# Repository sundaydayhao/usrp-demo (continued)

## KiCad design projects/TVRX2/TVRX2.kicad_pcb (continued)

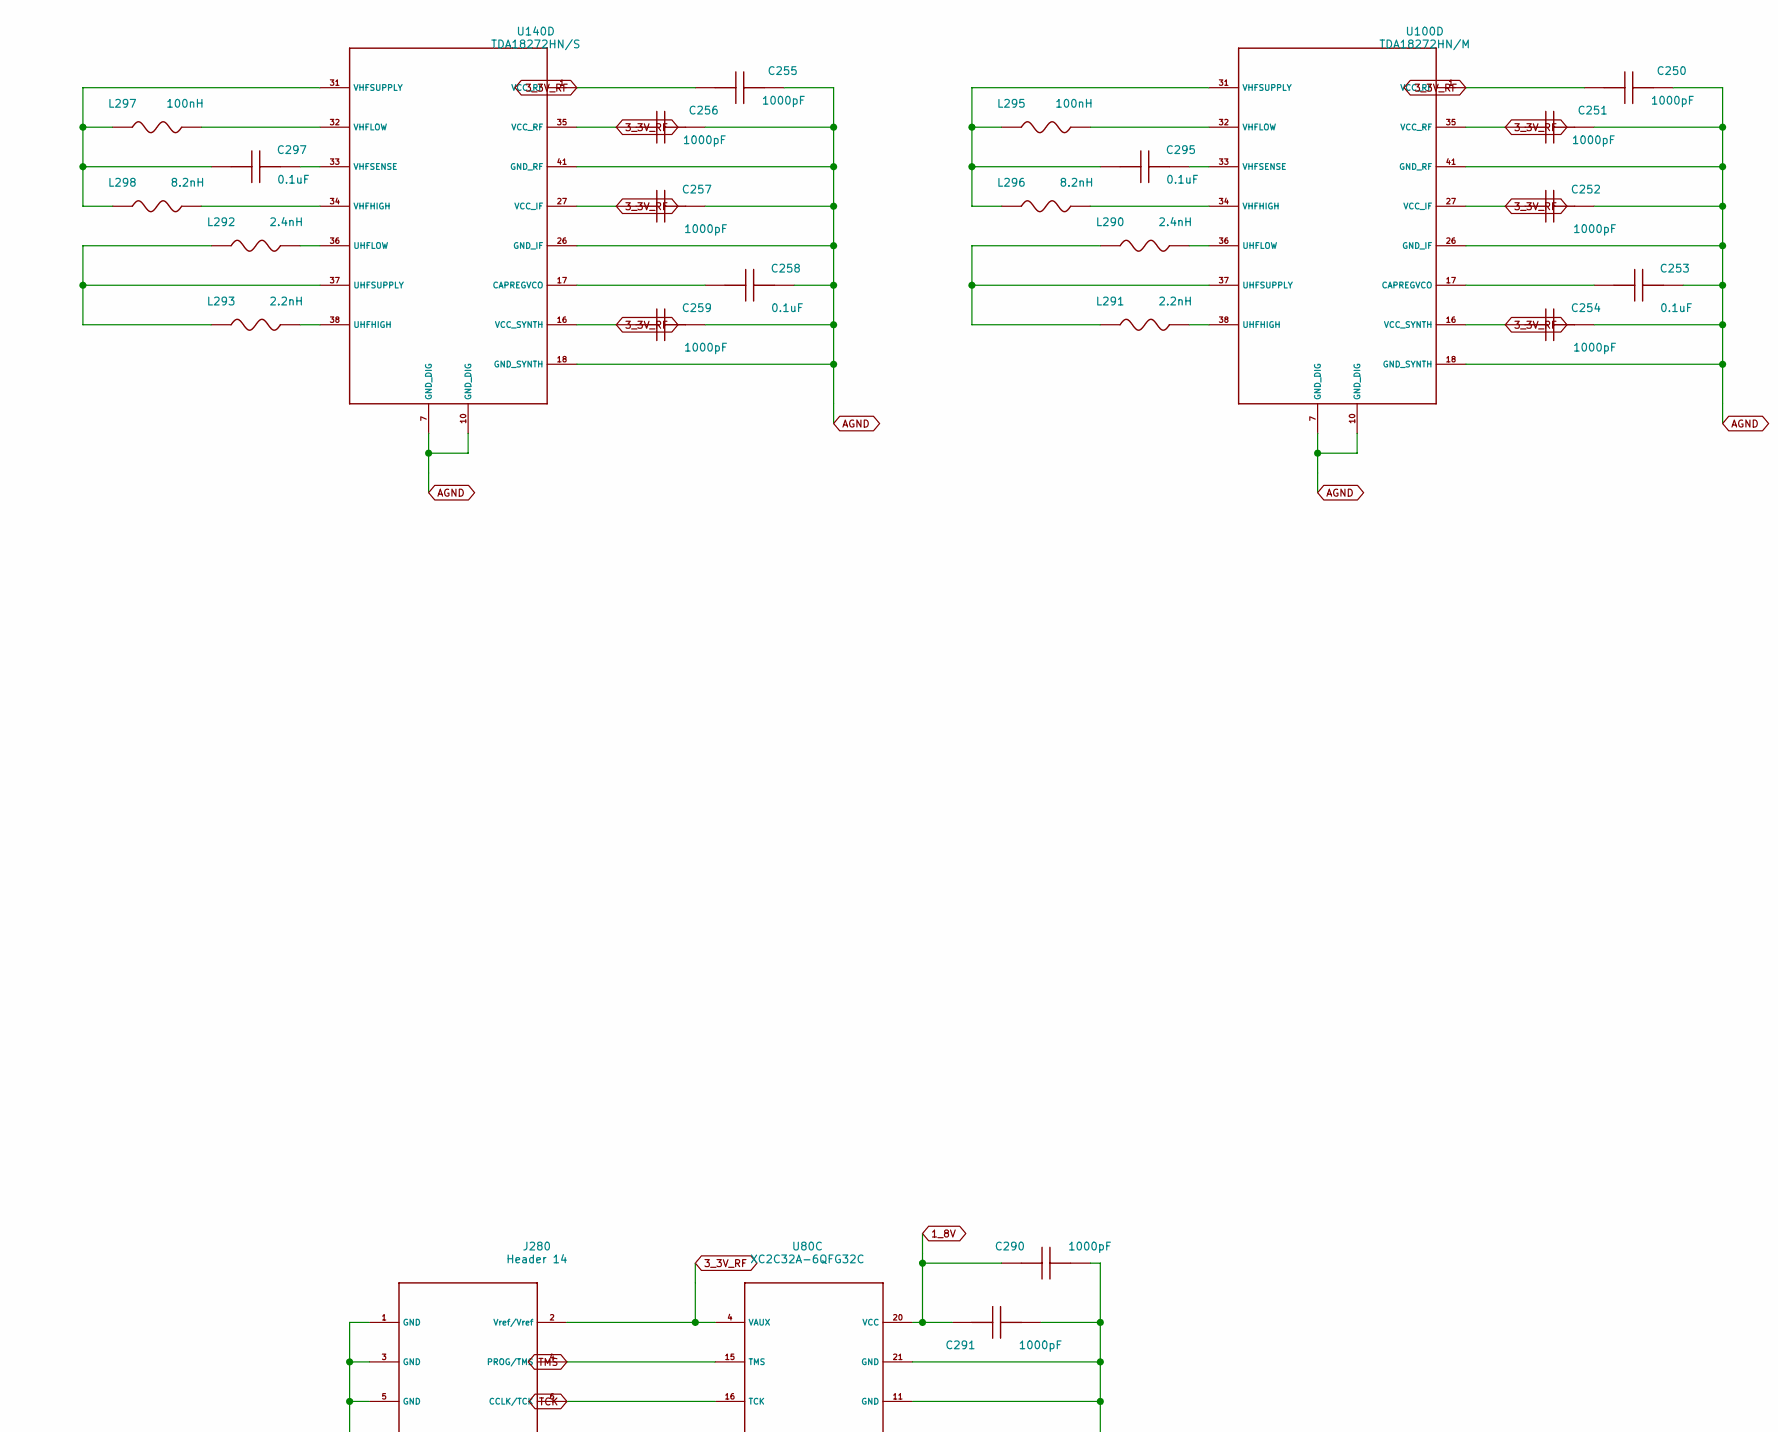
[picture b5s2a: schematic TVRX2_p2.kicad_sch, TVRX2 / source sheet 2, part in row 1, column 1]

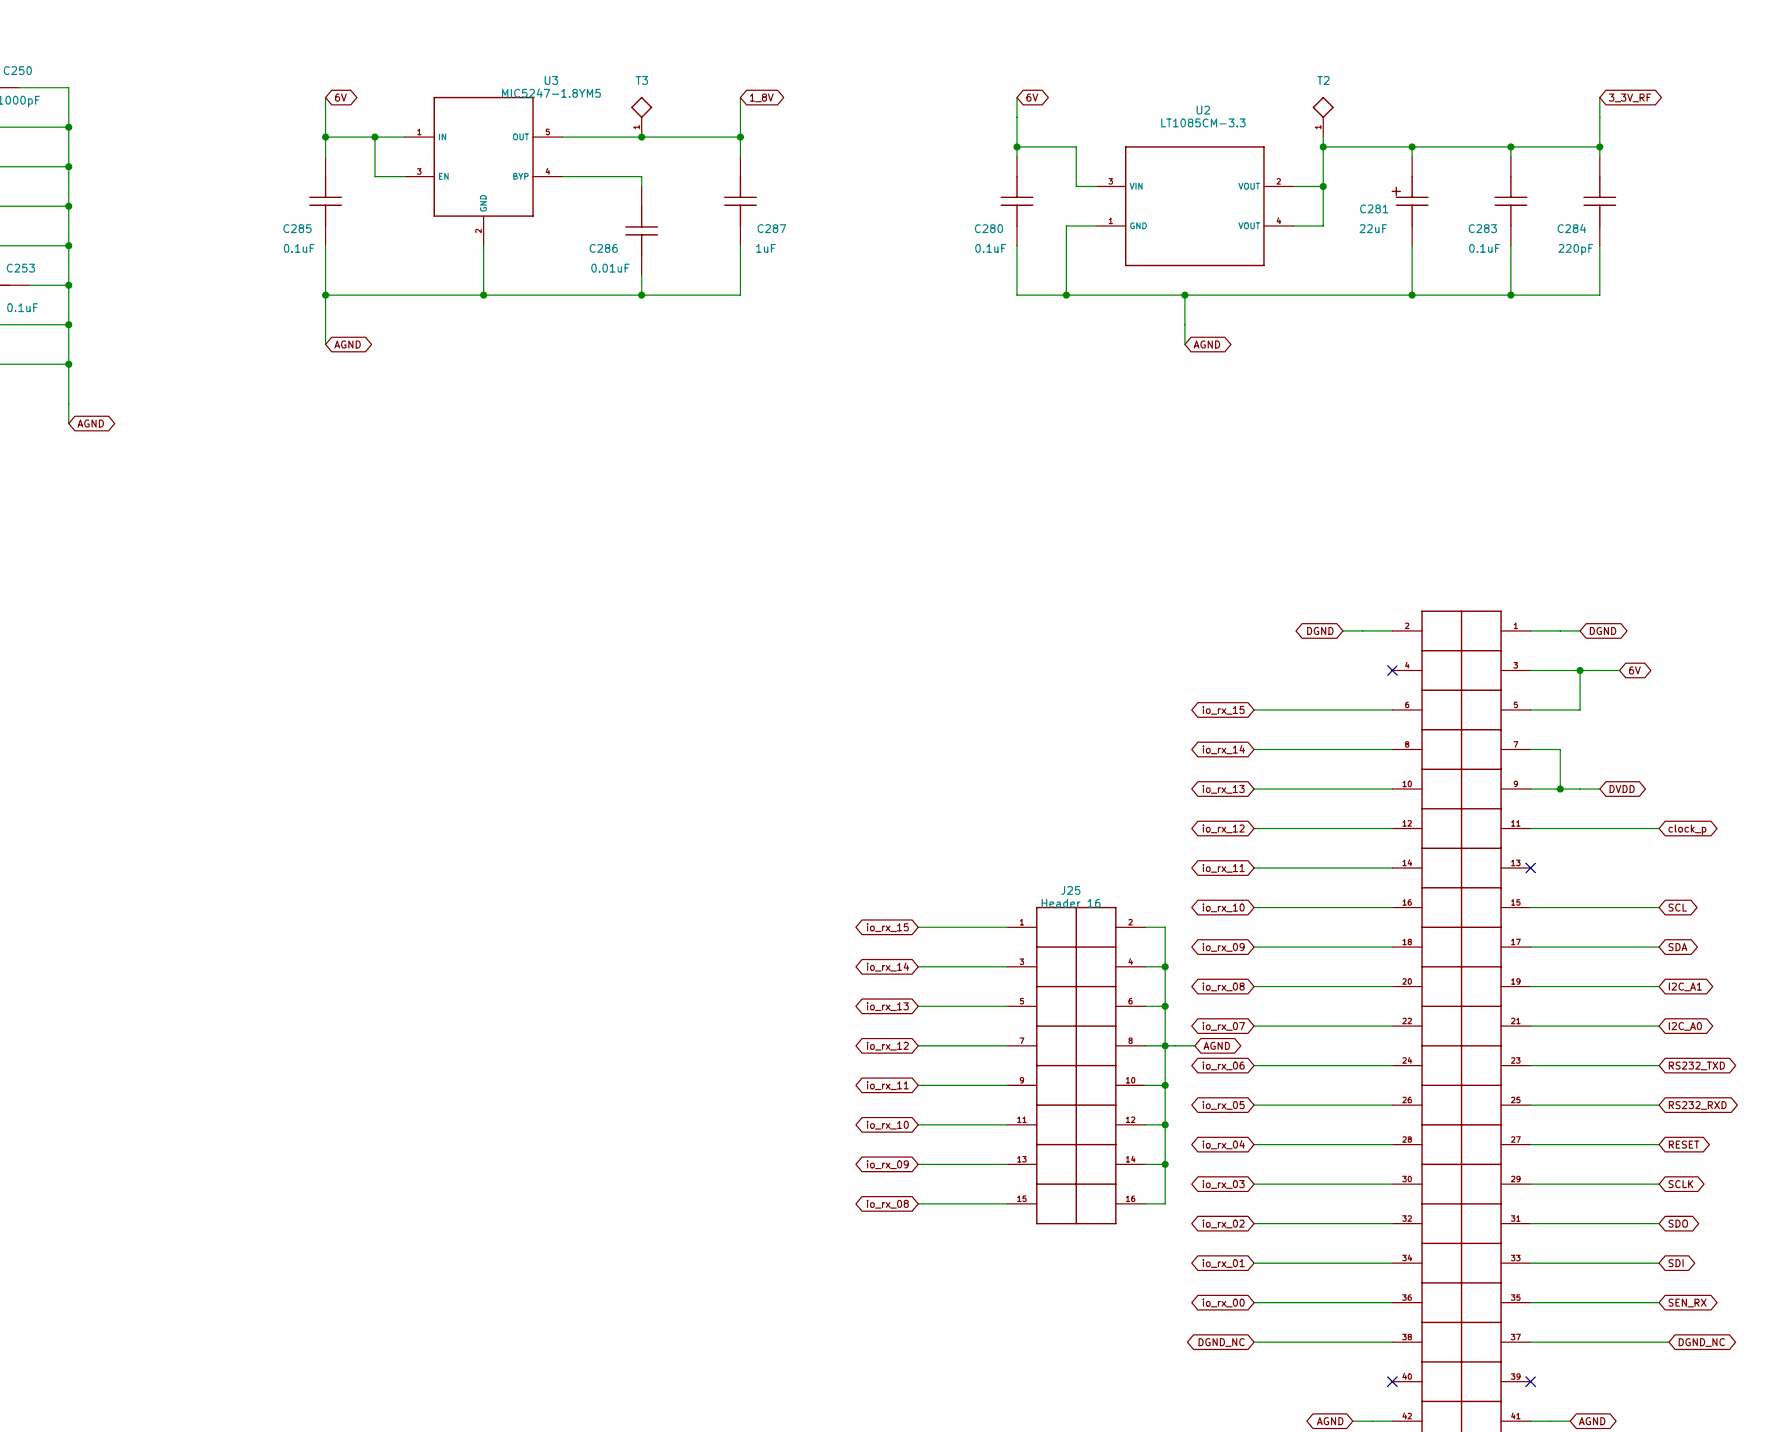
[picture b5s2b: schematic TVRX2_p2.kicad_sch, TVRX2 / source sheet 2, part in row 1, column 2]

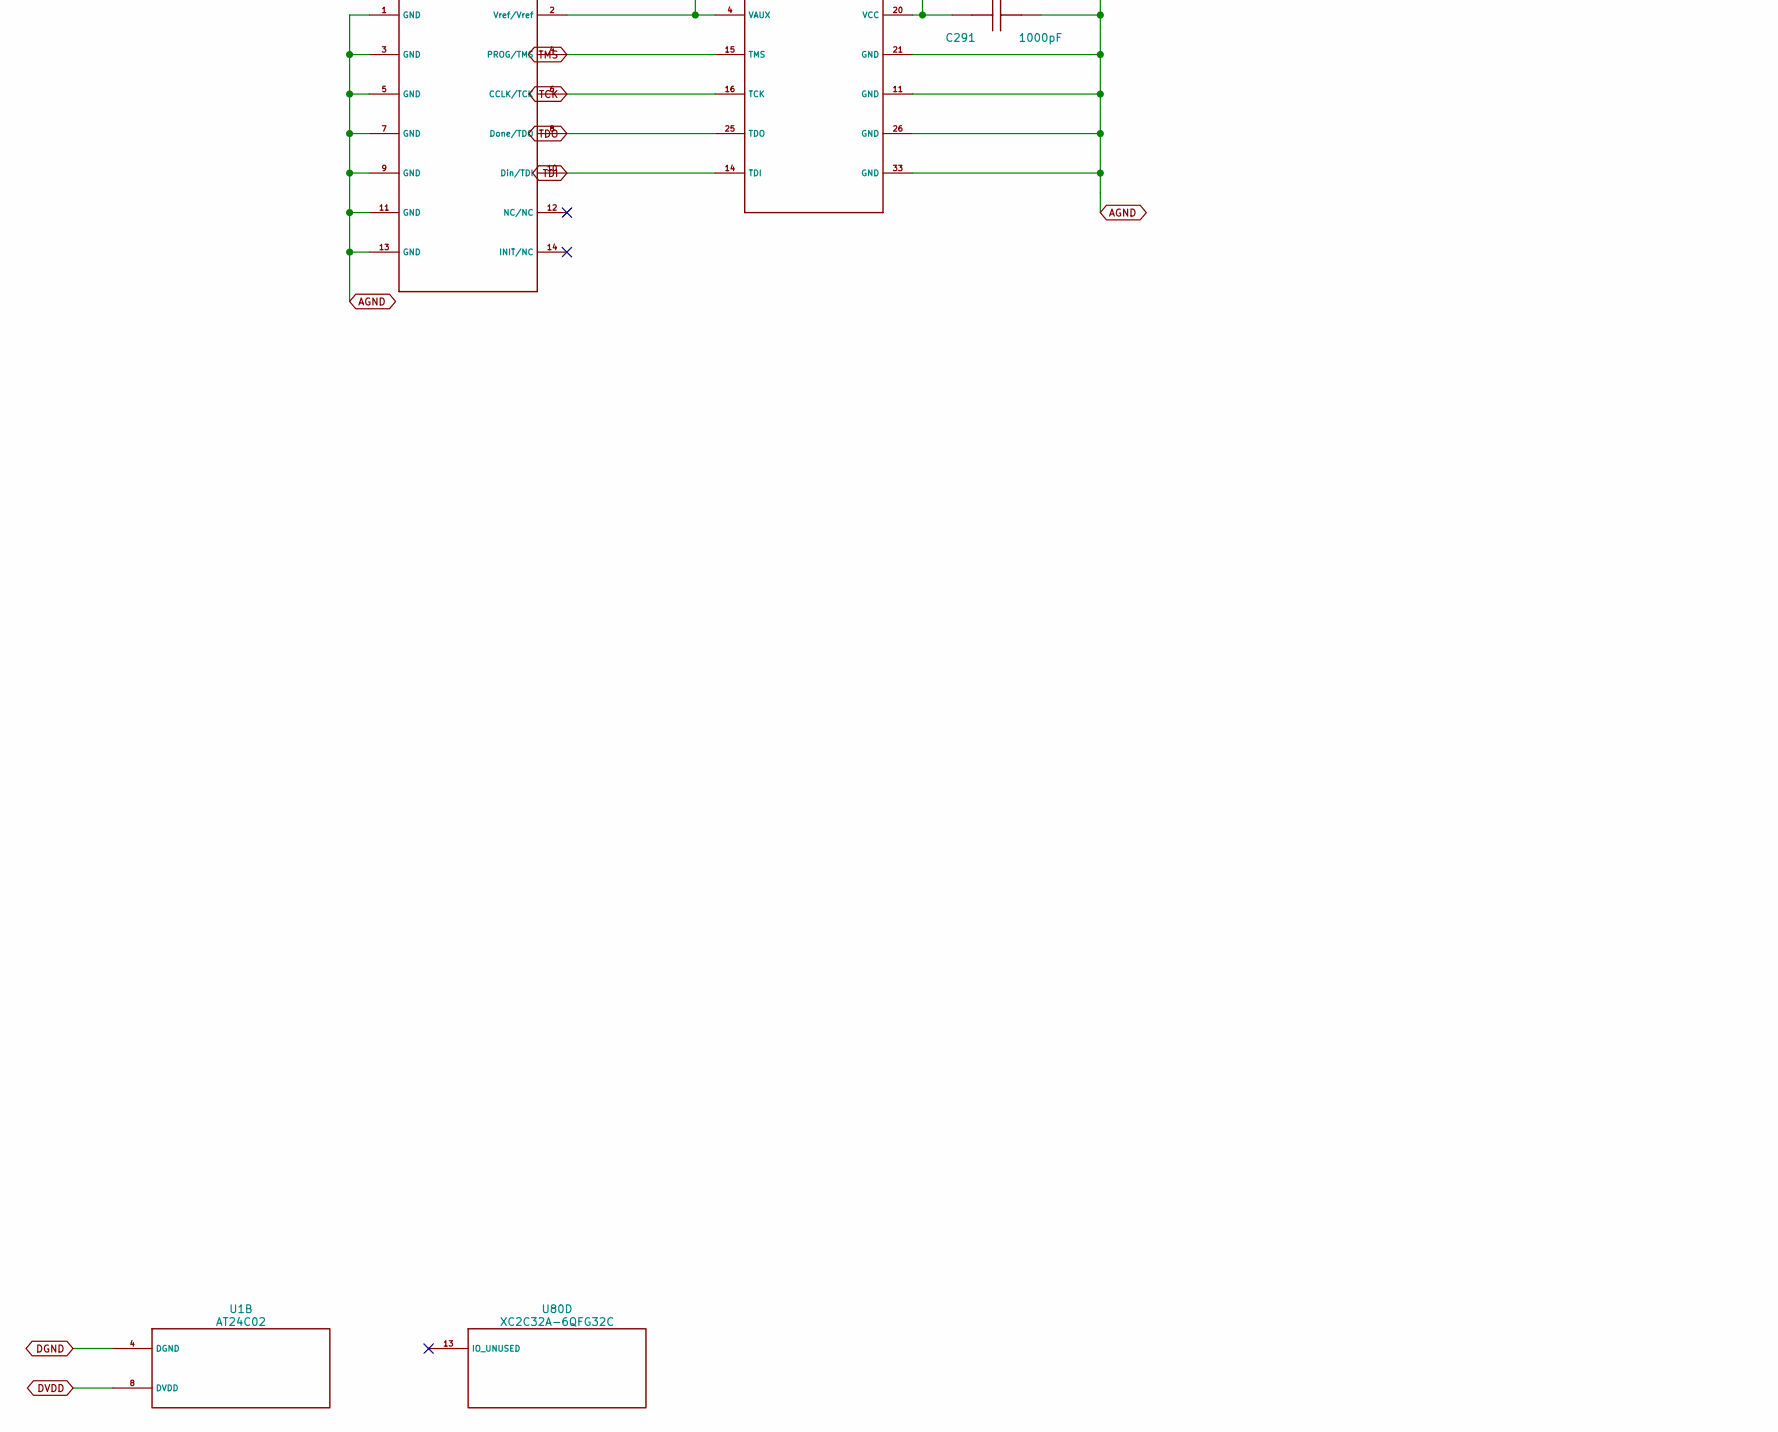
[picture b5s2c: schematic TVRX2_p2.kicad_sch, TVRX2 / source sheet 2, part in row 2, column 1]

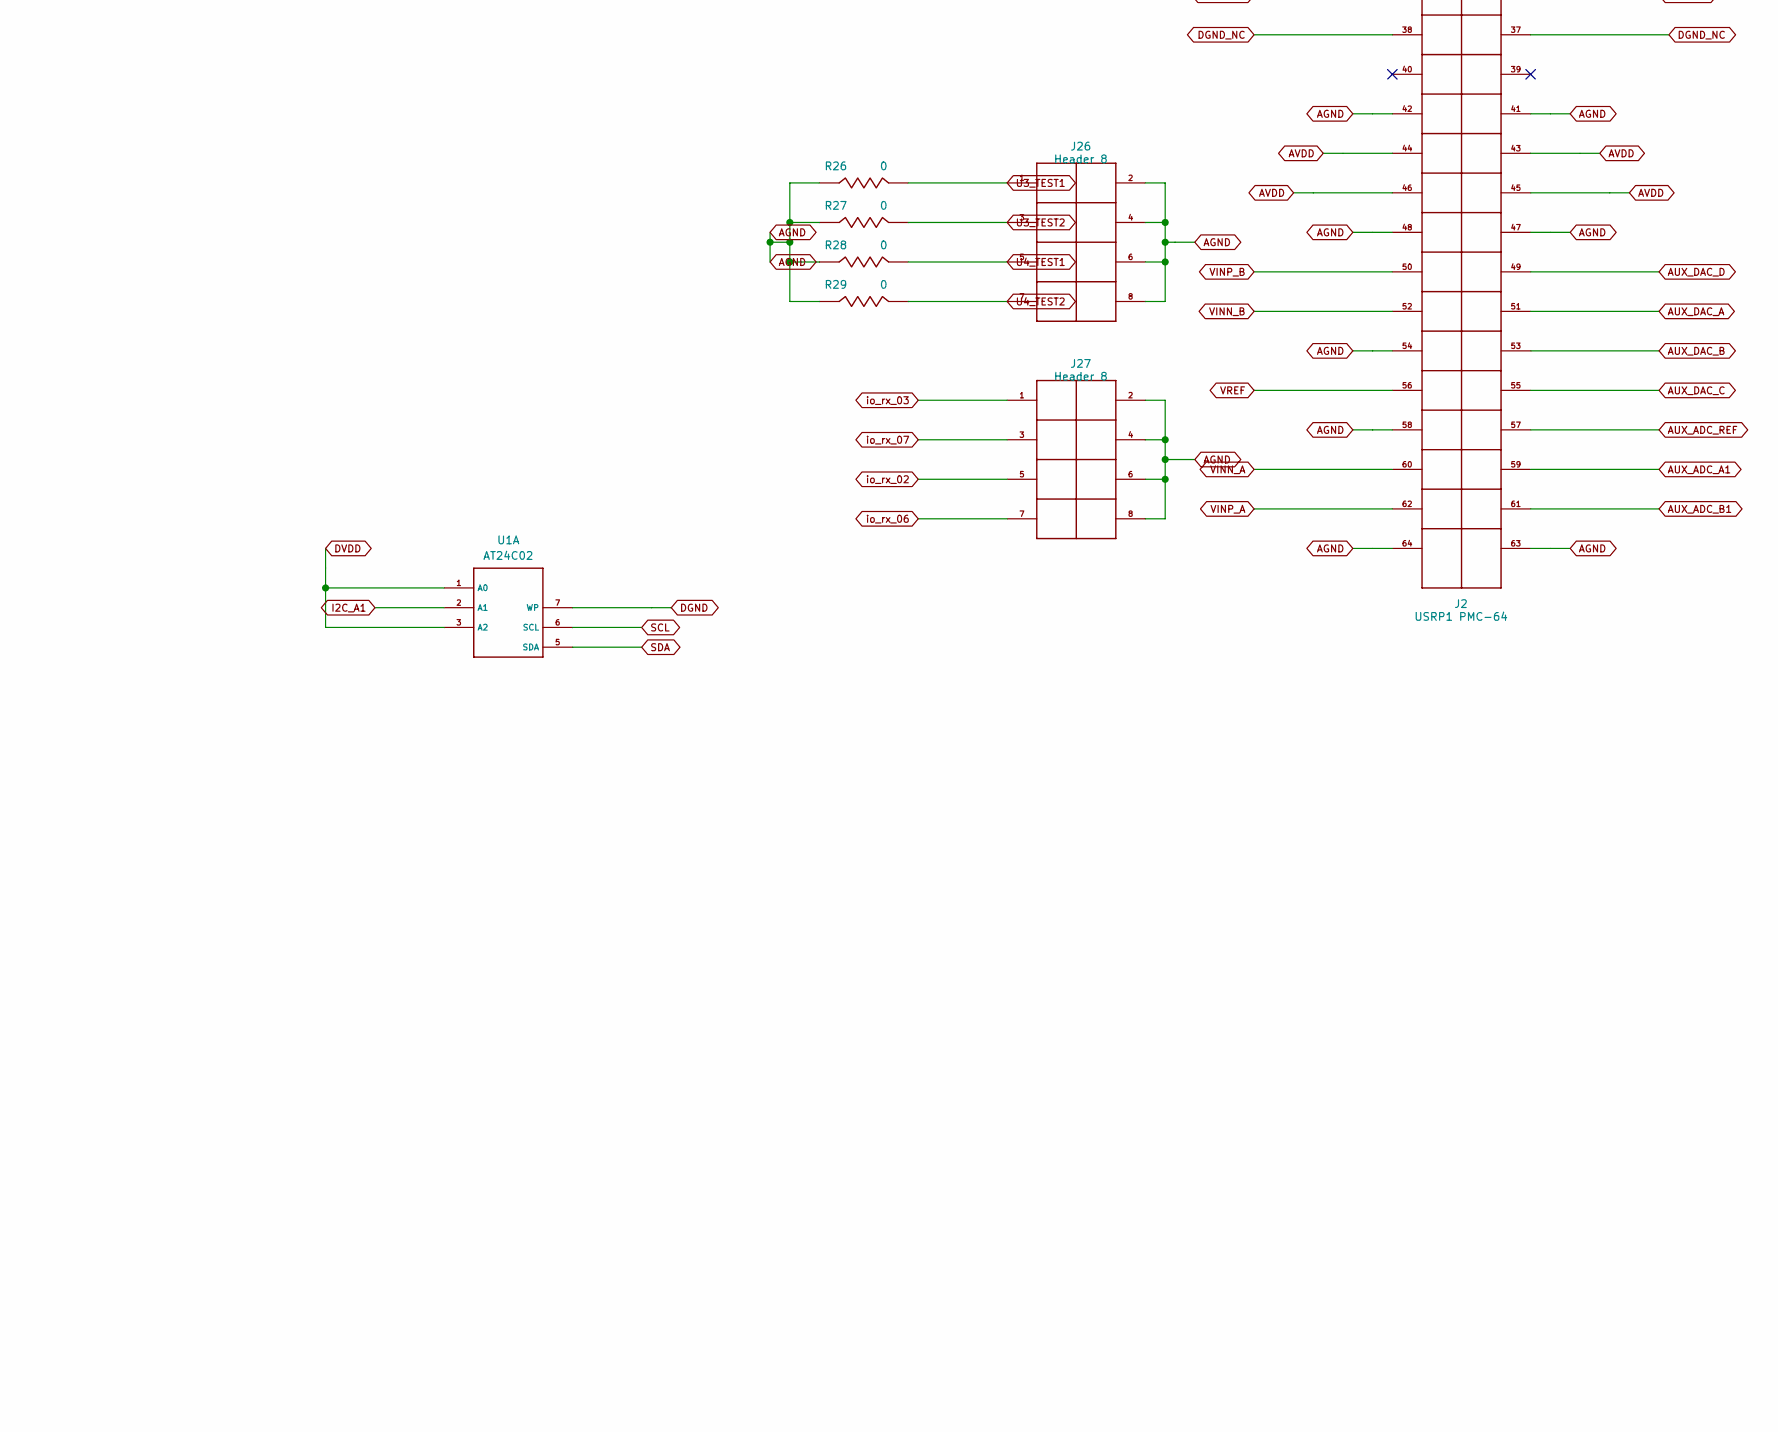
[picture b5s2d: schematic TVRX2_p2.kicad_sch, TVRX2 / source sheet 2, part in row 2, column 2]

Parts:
C250: 1000pF; C250
C251: 1000pF; C251
C252: 1000pF; C252
C253: 0.1uF; C253
C254: 1000pF; C254
C255: 1000pF; C255
C256: 1000pF; C256
C257: 1000pF; C257
C258: 0.1uF; C258
C259: 1000pF; C259
C280: 0.1uF; C280; MPN CL05B104KO5NNNC; LCSC C1525
C281: 22uF; C281
C283: 0.1uF; C283; MPN CL05B104KO5NNNC; LCSC C1525
C284: 220pF; C284
C285: 0.1uF; C285; MPN CL05B104KO5NNNC; LCSC C1525
C286: 0.01uF; C286
C287: 1uF; C287
C290: 1000pF; C290
C291: 1000pF; C291
C295: 0.1uF; C295
C297: 0.1uF; C297
J2: USRP1 PMC-64; J2
J25: Header 16; J25
J26: Header 8; J26
J27: Header 8; J27
J280: Header 14; J280
L290: 2.4nH; L290
L291: 2.2nH; L291
L292: 2.4nH; L292
L293: 2.2nH; L293
L295: 100nH; L295
L296: 8.2nH; L296
L297: 100nH; L297
L298: 8.2nH; L298
R26: 0; R26
R27: 0; R27
R28: 0; R28
R29: 0; R29
T2: TestPoint; T2
T3: TestPoint; T3
U1: AT24C02; U1; MPN AT24C02C-SSHM-T; LCSC C6203
U2: LT1085CM-3.3; U2; MPN LT1085CM-3.3
U3: MIC5247-1.8YM5; U3; MPN MIC5247-1.8YM5
U80: XC2C32A-6QFG32C; U80; MPN XC2C32A-6QFG32C
U100: TDA18272HN/M; U100; MPN TDA18272HN/M
U140: TDA18272HN/S; U140; MPN TDA18272HN/S

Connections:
1_8V: C287.1, C290.1, C291.1, T3.1, U3.5 (OUT), U80.20 (VCC)
3_3V_RF: C250.1, C251.1, C252.1, C254.1, C255.1, C256.1, C257.1, C259.1, C281.1, C283.1, C284.1, J280.2 (Vref/Vref), T2.1, U2.2 (VOUT), U2.4 (VOUT), U80.4 (VAUX), U100.1 (VCC_RF), U100.16 (VCC_SYNTH), U100.27 (VCC_IF), U100.35 (VCC_RF), U140.1 (VCC_RF), U140.16 (VCC_SYNTH), U140.27 (VCC_IF), U140.35 (VCC_RF); also elsewhere on the board
6V: C280.1, C285.1, J2.3, J2.5, U2.3 (VIN), U3.1 (IN), U3.3 (EN)
AGND: C250.2, C251.2, C252.2, C253.2, C254.2, C255.2, C256.2, C257.2, C258.2, C259.2, C280.2, C281.2, C283.2, C284.2, C285.2, C286.2, C287.2, C290.2, C291.2, J2.41, J2.42, J2.47, J2.48, J2.54, J2.58, J2.63, J2.64, J25.2, J25.4, J25.6, J25.8, J25.10, J25.12, J25.14, J25.16, J26.2, J26.4, J26.6, J26.8, J27.2, J27.4, J27.6, J27.8, J280.1 (GND), J280.3 (GND), J280.5 (GND), J280.7 (GND), J280.9 (GND), J280.11 (GND), J280.13 (GND), R26.1, R27.1, R28.1, R29.1, U2.1 (GND), U3.2 (GND), U80.11 (GND), U80.21 (GND), U80.26 (GND), U80.33 (GND), U100.7 (GND_DIG), U100.10 (GND_DIG), U100.18 (GND_SYNTH), U100.26 (GND_IF), U100.41 (GND_RF), U140.7 (GND_DIG), U140.10 (GND_DIG), U140.18 (GND_SYNTH), U140.26 (GND_IF), U140.41 (GND_RF); also elsewhere on the board
AUX_ADC_A1: J2.59
AUX_ADC_B1: J2.61
AUX_ADC_REF: J2.57
AUX_DAC_A: J2.51; also elsewhere on the board
AUX_DAC_B: J2.53; also elsewhere on the board
AUX_DAC_C: J2.55
AUX_DAC_D: J2.49
AVDD: J2.43, J2.44, J2.45, J2.46
DGND: J2.1, J2.2, U1.4 (DGND), U1.7 (WP)
DGND_NC: J2.37, J2.38
DVDD: J2.7, J2.9, U1.1 (A0), U1.3 (A2), U1.8 (DVDD)
I2C_A0: J2.21
I2C_A1: J2.19, U1.2 (A1)
unnamed: C286.1, U3.4 (BYP)
unnamed: C253.1, U100.17 (CAPREGVCO)
unnamed: L291.2, U100.38 (UHFHIGH)
unnamed: L290.2, U100.36 (UHFLOW)
unnamed: L290.1, L291.1, U100.37 (UHFSUPPLY)
unnamed: L296.2, U100.34 (VHFHIGH)
unnamed: L295.2, U100.32 (VHFLOW)
unnamed: C295.2, U100.33 (VHFSENSE)
unnamed: C295.1, L295.1, L296.1, U100.31 (VHFSUPPLY)
unnamed: C258.1, U140.17 (CAPREGVCO)
unnamed: L293.2, U140.38 (UHFHIGH)
unnamed: L292.2, U140.36 (UHFLOW)
unnamed: L292.1, L293.1, U140.37 (UHFSUPPLY)
unnamed: L298.2, U140.34 (VHFHIGH)
unnamed: L297.2, U140.32 (VHFLOW)
unnamed: C297.2, U140.33 (VHFSENSE)
unnamed: C297.1, L297.1, L298.1, U140.31 (VHFSUPPLY)
RESET: J2.27
RS232_RXD: J2.25
RS232_TXD: J2.23
SCL: J2.15, U1.6 (SCL); also elsewhere on the board
SCLK: J2.29
SDA: J2.17, U1.5 (SDA); also elsewhere on the board
SDI: J2.33
SDO: J2.31
SEN_RX: J2.35
TCK: J280.6 (CCLK/TCK), U80.16 (TCK)
TDI: J280.10 (Din/TDI), U80.14 (TDI)
TDO: J280.8 (Done/TDO), U80.25 (TDO)
TMS: J280.4 (PROG/TMS), U80.15 (TMS)
U3_TEST1: J26.1, R26.2; also elsewhere on the board
U3_TEST2: J26.3, R27.2; also elsewhere on the board
U4_TEST1: J26.5, R28.2; also elsewhere on the board
U4_TEST2: J26.7, R29.2; also elsewhere on the board
VINN_A: J2.60; also elsewhere on the board
VINN_B: J2.52; also elsewhere on the board
VINP_A: J2.62; also elsewhere on the board
VINP_B: J2.50; also elsewhere on the board
VREF: J2.56
clock_p: J2.11; also elsewhere on the board
io_rx_00: J2.36; also elsewhere on the board
io_rx_01: J2.34; also elsewhere on the board
io_rx_02: J2.32, J27.5; also elsewhere on the board
io_rx_03: J2.30, J27.1; also elsewhere on the board
io_rx_04: J2.28; also elsewhere on the board
io_rx_05: J2.26; also elsewhere on the board
io_rx_06: J2.24, J27.7; also elsewhere on the board
io_rx_07: J2.22, J27.3; also elsewhere on the board
io_rx_08: J2.20, J25.15; also elsewhere on the board
io_rx_09: J2.18, J25.13; also elsewhere on the board
io_rx_10: J2.16, J25.11; also elsewhere on the board
io_rx_11: J2.14, J25.9
io_rx_12: J2.12, J25.7
io_rx_13: J2.10, J25.5
io_rx_14: J2.8, J25.3
io_rx_15: J2.6, J25.1

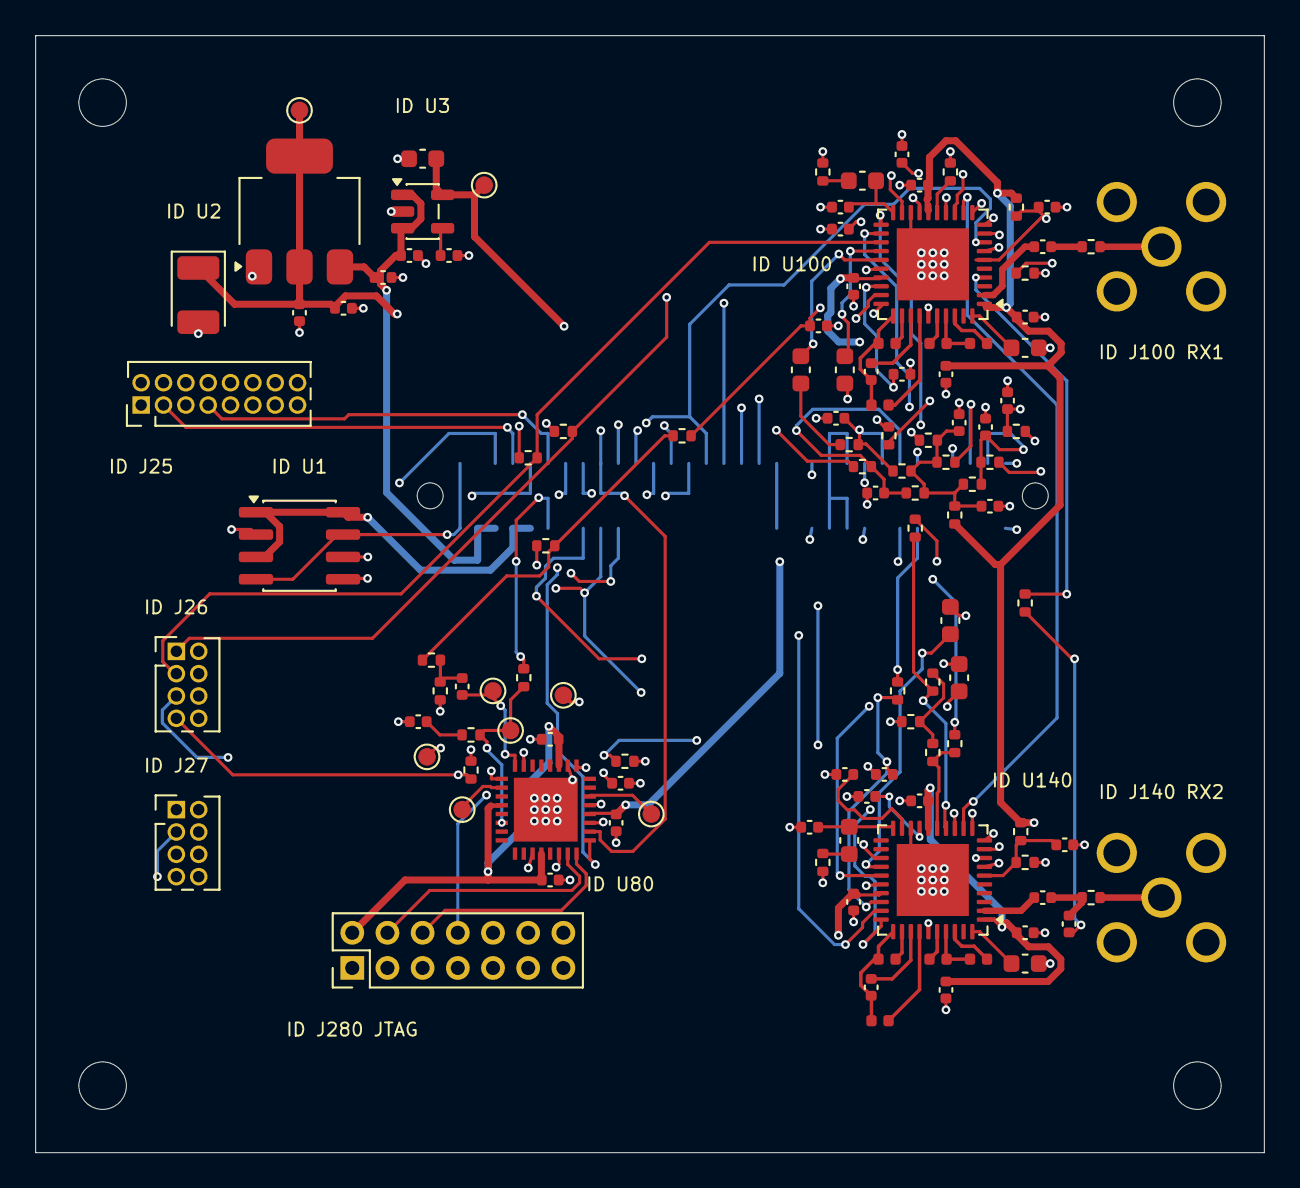
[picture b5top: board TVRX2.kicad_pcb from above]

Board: 4 copper layers, 69.8 x 63.5 mm, 121 parts (1 on the bottom side), 104 nets.

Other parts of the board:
H1, H2, H3, H4: MountingHole_2.7mm_M2.5

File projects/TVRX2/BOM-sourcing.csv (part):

Reference,Value,Footprint,Manufacturer,MPN,LCSC,Sourcing_status,Specification,Source_value,Evidence,Approved_brands,Sourcing_policy
C102,1000pF,USRP:C102,候选：Murata / TDK / Samsung Electro-Mechanics / Walsin / FH / EYANG,,,0402 按参数选型，待锁定料号,0402; 匹配和调谐电容用 C0G，保留原容差；去耦用 X7R >=16 V,1000pF,,Murata / TDK / Samsung Electro-Mechanics / Walsin / FH / EYANG,国产与国际品牌均可；满足参数后比较含税到手价、起订量、库存和交期；换料须复核封装及电气指标
C103,1uF,USRP:C103,候选：Murata / TDK / Samsung Electro-Mechanics / Walsin / FH / EYANG,,,规格选型，待锁定料号,按项目焊盘尺寸；RF/匹配/PLL环路优先 C0G；去耦 X7R；耐压 >=16 V；保留原容差,1uF,,Murata / TDK / Samsung Electro-Mechanics / Walsin / FH / EYANG,国产与国际品牌均可；满足参数后比较含税到手价、起订量、库存和交期；换料须复核封装及电气指标
C104,1uF,USRP:C104,候选：Murata / TDK / Samsung Electro-Mechanics / Walsin / FH / EYANG,,,规格选型，待锁定料号,按项目焊盘尺寸；RF/匹配/PLL环路优先 C0G；去耦 X7R；耐压 >=16 V；保留原容差,1uF,,Murata / TDK / Samsung Electro-Mechanics / Walsin / FH / EYANG,国产与国际品牌均可；满足参数后比较含税到手价、起订量、库存和交期；换料须复核封装及电气指标
C109,100pF,USRP:C109,候选：Murata / TDK / Samsung Electro-Mechanics / Walsin / FH / EYANG,,,0402 按参数选型，待锁定料号,0402; 匹配和调谐电容用 C0G，保留原容差；去耦用 X7R >=16 V,100pF,,Murata / TDK / Samsung Electro-Mechanics / Walsin / FH / EYANG,国产与国际品牌均可；满足参数后比较含税到手价、起订量、库存和交期；换料须复核封装及电气指标
C110,100pF,USRP:C110,候选：Murata / TDK / Samsung Electro-Mechanics / Walsin / FH / EYANG,,,0402 按参数选型，待锁定料号,0402; 匹配和调谐电容用 C0G，保留原容差；去耦用 X7R >=16 V,100pF,,Murata / TDK / Samsung Electro-Mechanics / Walsin / FH / EYANG,国产与国际品牌均可；满足参数后比较含税到手价、起订量、库存和交期；换料须复核封装及电气指标
C111,0.22uF,USRP:C111,候选：Murata / TDK / Samsung Electro-Mechanics / Walsin / FH / EYANG,,,规格选型，待锁定料号,按项目焊盘尺寸；RF/匹配/PLL环路优先 C0G；去耦 X7R；耐压 >=16 V；保留原容差,0.22uF,,Murata / TDK / Samsung Electro-Mechanics / Walsin / FH / EYANG,国产与国际品牌均可；满足参数后比较含税到手价、起订量、库存和交期；换料须复核封装及电气指标
C112,4700pF,USRP:C112,候选：Murata / TDK / Samsung Electro-Mechanics / Walsin / FH / EYANG,,,0402 按参数选型，待锁定料号,0402; 匹配和调谐电容用 C0G，保留原容差；去耦用 X7R >=16 V,4700pF,,Murata / TDK / Samsung Electro-Mechanics / Walsin / FH / EYANG,国产与国际品牌均可；满足参数后比较含税到手价、起订量、库存和交期；换料须复核封装及电气指标
C120,2700pF,USRP:C120,候选：Murata / TDK / Samsung Electro-Mechanics / Walsin / FH / EYANG,,,0402 按参数选型，待锁定料号,0402; 匹配和调谐电容用 C0G，保留原容差；去耦用 X7R >=16 V,2700pF,,Murata / TDK / Samsung Electro-Mechanics / Walsin / FH / EYANG,国产与国际品牌均可；满足参数后比较含税到手价、起订量、库存和交期；换料须复核封装及电气指标
C121,6800pF,USRP:C121,候选：Murata / TDK / Samsung Electro-Mechanics / Walsin / FH / EYANG,,,0402 按参数选型，待锁定料号,0402; 匹配和调谐电容用 C0G，保留原容差；去耦用 X7R >=16 V,6800pF,,Murata / TDK / Samsung Electro-Mechanics / Walsin / FH / EYANG,国产与国际品牌均可；满足参数后比较含税到手价、起订量、库存和交期；换料须复核封装及电气指标
C122,0.22uF,USRP:C122,候选：Murata / TDK / Samsung Electro-Mechanics / Walsin / FH / EYANG,,,规格选型，待锁定料号,按项目焊盘尺寸；RF/匹配/PLL环路优先 C0G；去耦 X7R；耐压 >=16 V；保留原容差,0.22uF,,Murata / TDK / Samsung Electro-Mechanics / Walsin / FH / EYANG,国产与国际品牌均可；满足参数后比较含税到手价、起订量、库存和交期；换料须复核封装及电气指标
C130,NONE,USRP:C130,,,,DNP 不装,保留调试/选配焊盘,NONE,,,
C142,1000pF,USRP:C142,候选：Murata / TDK / Samsung Electro-Mechanics / Walsin / FH / EYANG,,,0402 按参数选型，待锁定料号,0402; 匹配和调谐电容用 C0G，保留原容差；去耦用 X7R >=16 V,1000pF,,Murata / TDK / Samsung Electro-Mechanics / Walsin / FH / EYANG,国产与国际品牌均可；满足参数后比较含税到手价、起订量、库存和交期；换料须复核封装及电气指标
C143,1uF,USRP:C143,候选：Murata / TDK / Samsung Electro-Mechanics / Walsin / FH / EYANG,,,规格选型，待锁定料号,按项目焊盘尺寸；RF/匹配/PLL环路优先 C0G；去耦 X7R；耐压 >=16 V；保留原容差,1uF,,Murata / TDK / Samsung Electro-Mechanics / Walsin / FH / EYANG,国产与国际品牌均可；满足参数后比较含税到手价、起订量、库存和交期；换料须复核封装及电气指标
C144,1uF,USRP:C144,候选：Murata / TDK / Samsung Electro-Mechanics / Walsin / FH / EYANG,,,规格选型，待锁定料号,按项目焊盘尺寸；RF/匹配/PLL环路优先 C0G；去耦 X7R；耐压 >=16 V；保留原容差,1uF,,Murata / TDK / Samsung Electro-Mechanics / Walsin / FH / EYANG,国产与国际品牌均可；满足参数后比较含税到手价、起订量、库存和交期；换料须复核封装及电气指标
C149,100pF,USRP:C149,候选：Murata / TDK / Samsung Electro-Mechanics / Walsin / FH / EYANG,,,0402 按参数选型，待锁定料号,0402; 匹配和调谐电容用 C0G，保留原容差；去耦用 X7R >=16 V,100pF,,Murata / TDK / Samsung Electro-Mechanics / Walsin / FH / EYANG,国产与国际品牌均可；满足参数后比较含税到手价、起订量、库存和交期；换料须复核封装及电气指标
C150,100pF,USRP:C150,候选：Murata / TDK / Samsung Electro-Mechanics / Walsin / FH / EYANG,,,0402 按参数选型，待锁定料号,0402; 匹配和调谐电容用 C0G，保留原容差；去耦用 X7R >=16 V,100pF,,Murata / TDK / Samsung Electro-Mechanics / Walsin / FH / EYANG,国产与国际品牌均可；满足参数后比较含税到手价、起订量、库存和交期；换料须复核封装及电气指标
C151,0.22uF,USRP:C151,候选：Murata / TDK / Samsung Electro-Mechanics / Walsin / FH / EYANG,,,规格选型，待锁定料号,按项目焊盘尺寸；RF/匹配/PLL环路优先 C0G；去耦 X7R；耐压 >=16 V；保留原容差,0.22uF,,Murata / TDK / Samsung Electro-Mechanics / Walsin / FH / EYANG,国产与国际品牌均可；满足参数后比较含税到手价、起订量、库存和交期；换料须复核封装及电气指标
C152,4700pF,USRP:C152,候选：Murata / TDK / Samsung Electro-Mechanics / Walsin / FH / EYANG,,,0402 按参数选型，待锁定料号,0402; 匹配和调谐电容用 C0G，保留原容差；去耦用 X7R >=16 V,4700pF,,Murata / TDK / Samsung Electro-Mechanics / Walsin / FH / EYANG,国产与国际品牌均可；满足参数后比较含税到手价、起订量、库存和交期；换料须复核封装及电气指标
C153,NONE,USRP:C153,,,,DNP 不装,保留调试/选配焊盘,NONE,,,
C160,2700pF,USRP:C160,候选：Murata / TDK / Samsung Electro-Mechanics / Walsin / FH / EYANG,,,0402 按参数选型，待锁定料号,0402; 匹配和调谐电容用 C0G，保留原容差；去耦用 X7R >=16 V,2700pF,,Murata / TDK / Samsung Electro-Mechanics / Walsin / FH / EYANG,国产与国际品牌均可；满足参数后比较含税到手价、起订量、库存和交期；换料须复核封装及电气指标
C161,6800pF,USRP:C161,候选：Murata / TDK / Samsung Electro-Mechanics / Walsin / FH / EYANG,,,0402 按参数选型，待锁定料号,0402; 匹配和调谐电容用 C0G，保留原容差；去耦用 X7R >=16 V,6800pF,,Murata / TDK / Samsung Electro-Mechanics / Walsin / FH / EYANG,国产与国际品牌均可；满足参数后比较含税到手价、起订量、库存和交期；换料须复核封装及电气指标
C162,0.22uF,USRP:C162,候选：Murata / TDK / Samsung Electro-Mechanics / Walsin / FH / EYANG,,,规格选型，待锁定料号,按项目焊盘尺寸；RF/匹配/PLL环路优先 C0G；去耦 X7R；耐压 >=16 V；保留原容差,0.22uF,,Murata / TDK / Samsung Electro-Mechanics / Walsin / FH / EYANG,国产与国际品牌均可；满足参数后比较含税到手价、起订量、库存和交期；换料须复核封装及电气指标
C170,NONE,USRP:C170,,,,DNP 不装,保留调试/选配焊盘,NONE,,,
C181,0.1uF,USRP:C181,Samsung Electro-Mechanics,CL05B104KO5NNNC,C1525,已核对0402与电源对地去耦连接；待实机电源噪声验证,0402; 100 nF; X7R; 16 V; +/-10%; 电源去耦；需考虑直流偏压降容,0.1uF,https://datasheet.lcsc.com/datasheet/pdf/02336ea48ea44ca18c7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,Murata / TDK / Samsung Electro-Mechanics / Walsin / FH / EYANG,国产与国际品牌均可；满足参数后比较含税到手价、起订量、库存和交期；换料须复核封装及电气指标
C182,0.1uF,USRP:C182,Samsung Electro-Mechanics,CL05B104KO5NNNC,C1525,已核对0402与电源对地去耦连接；待实机电源噪声验证,0402; 100 nF; X7R; 16 V; +/-10%; 电源去耦；需考虑直流偏压降容,0.1uF,https://datasheet.lcsc.com/datasheet/pdf/02336ea48ea44ca18c7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,Murata / TDK / Samsung Electro-Mechanics / Walsin / FH / EYANG,国产与国际品牌均可；满足参数后比较含税到手价、起订量、库存和交期；换料须复核封装及电气指标
C183,1000pF,USRP:C183,候选：Murata / TDK / Samsung Electro-Mechanics / Walsin / FH / EYANG,,,0402 按参数选型，待锁定料号,0402; 匹配和调谐电容用 C0G，保留原容差；去耦用 X7R >=16 V,1000pF,,Murata / TDK / Samsung Electro-Mechanics / Walsin / FH / EYANG,国产与国际品牌均可；满足参数后比较含税到手价、起订量、库存和交期；换料须复核封装及电气指标
C184,NONE,USRP:C184,,,,DNP 不装,保留调试/选配焊盘,NONE,,,
C185,0.1uF,USRP:C185,候选：Murata / TDK / Samsung Electro-Mechanics / Walsin / FH / EYANG,,,0402 按参数选型，待锁定料号,0402; 匹配和调谐电容用 C0G，保留原容差；去耦用 X7R >=16 V,0.1uF,,Murata / TDK / Samsung Electro-Mechanics / Walsin / FH / EYANG,国产与国际品牌均可；满足参数后比较含税到手价、起订量、库存和交期；换料须复核封装及电气指标
C250,1000pF,USRP:C250,候选：Murata / TDK / Samsung Electro-Mechanics / Walsin / FH / EYANG,,,0402 按参数选型，待锁定料号,0402; 匹配和调谐电容用 C0G，保留原容差；去耦用 X7R >=16 V,1000pF,,Murata / TDK / Samsung Electro-Mechanics / Walsin / FH / EYANG,国产与国际品牌均可；满足参数后比较含税到手价、起订量、库存和交期；换料须复核封装及电气指标
C251,1000pF,USRP:C251,候选：Murata / TDK / Samsung Electro-Mechanics / Walsin / FH / EYANG,,,0402 按参数选型，待锁定料号,0402; 匹配和调谐电容用 C0G，保留原容差；去耦用 X7R >=16 V,1000pF,,Murata / TDK / Samsung Electro-Mechanics / Walsin / FH / EYANG,国产与国际品牌均可；满足参数后比较含税到手价、起订量、库存和交期；换料须复核封装及电气指标
C252,1000pF,USRP:C252,候选：Murata / TDK / Samsung Electro-Mechanics / Walsin / FH / EYANG,,,0402 按参数选型，待锁定料号,0402; 匹配和调谐电容用 C0G，保留原容差；去耦用 X7R >=16 V,1000pF,,Murata / TDK / Samsung Electro-Mechanics / Walsin / FH / EYANG,国产与国际品牌均可；满足参数后比较含税到手价、起订量、库存和交期；换料须复核封装及电气指标
C253,0.1uF,USRP:C253,候选：Murata / TDK / Samsung Electro-Mechanics / Walsin / FH / EYANG,,,0402 按参数选型，待锁定料号,0402; 匹配和调谐电容用 C0G，保留原容差；去耦用 X7R >=16 V,0.1uF,,Murata / TDK / Samsung Electro-Mechanics / Walsin / FH / EYANG,国产与国际品牌均可；满足参数后比较含税到手价、起订量、库存和交期；换料须复核封装及电气指标
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
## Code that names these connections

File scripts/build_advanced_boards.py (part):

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   num,rr,pn=bypass[ref];anchors=[(num,xy(allpads[rr][pn]),rr)]
  if not anchors:
   # Prefer a local active device; keep bypass components on their relevant rail.
   relevant={pin_net.get((ref,num)) for num in allpads[ref]}-{'AGND','DGND','DGND_RX','DGND_TX',None}
   eligible=[r for r in assigned if r.startswith('U') and any(pin_net.get((r,pn)) in relevant for pn in allpads[r])]
   page=model['components'][ref]['source_pages'][0]
   if name=='WBX':eligible=[r for r in eligible if set(model['components'][r]['source_pages'])&set(model['components'][ref]['source_pages'])] or eligible
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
